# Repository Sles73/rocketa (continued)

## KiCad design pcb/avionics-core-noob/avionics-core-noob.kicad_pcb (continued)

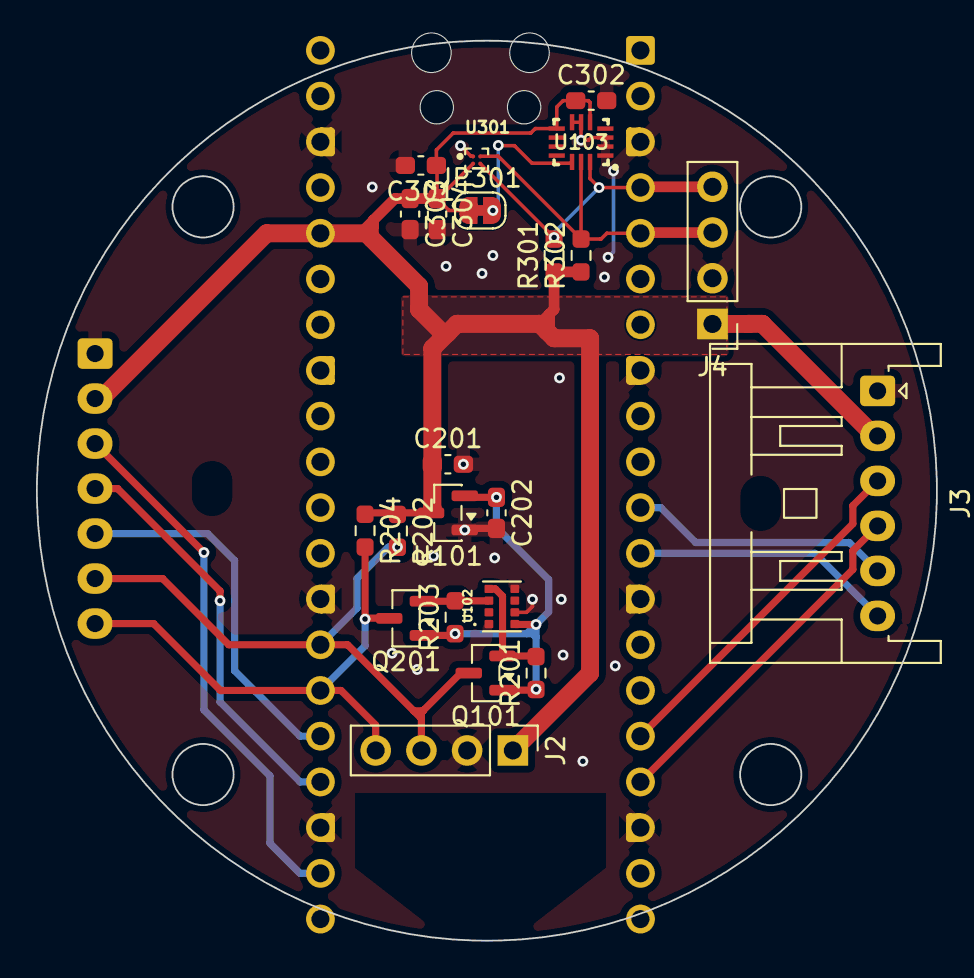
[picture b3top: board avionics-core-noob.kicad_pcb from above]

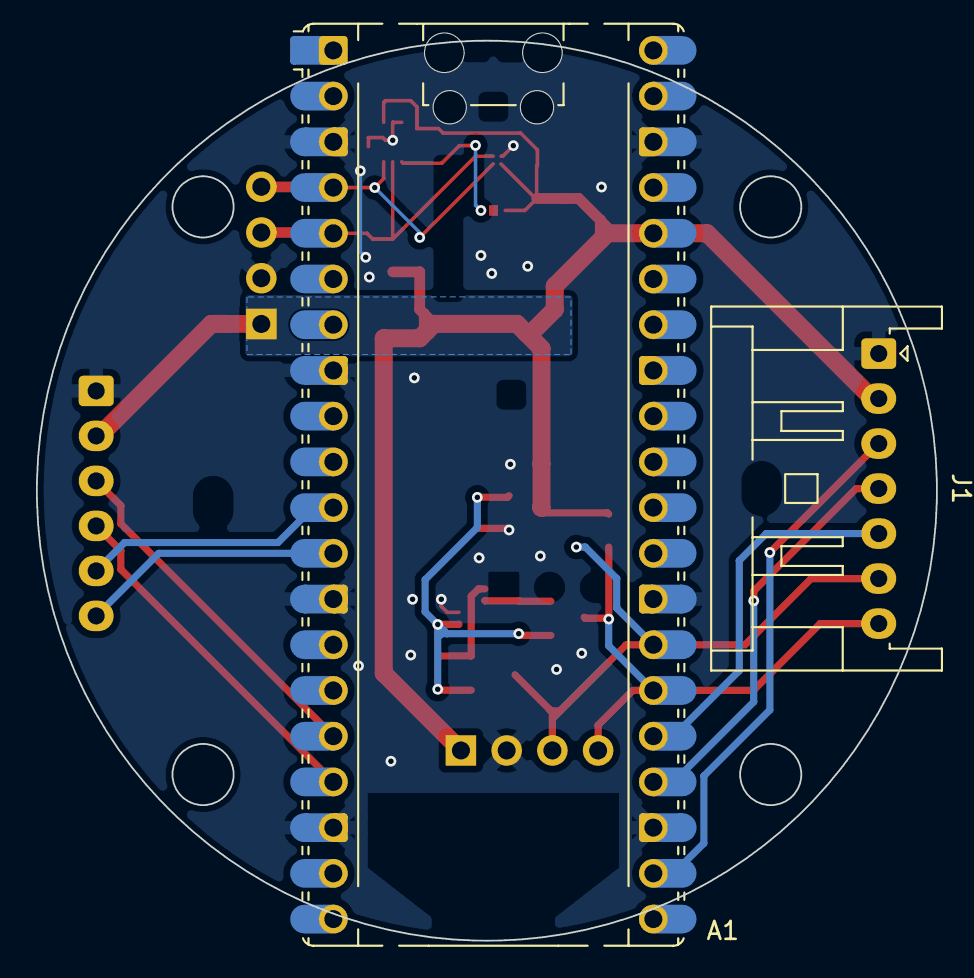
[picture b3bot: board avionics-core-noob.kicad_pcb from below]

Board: 2 copper layers, 50.0 x 50.0 mm, 24 parts (2 on the bottom side), 17 nets.

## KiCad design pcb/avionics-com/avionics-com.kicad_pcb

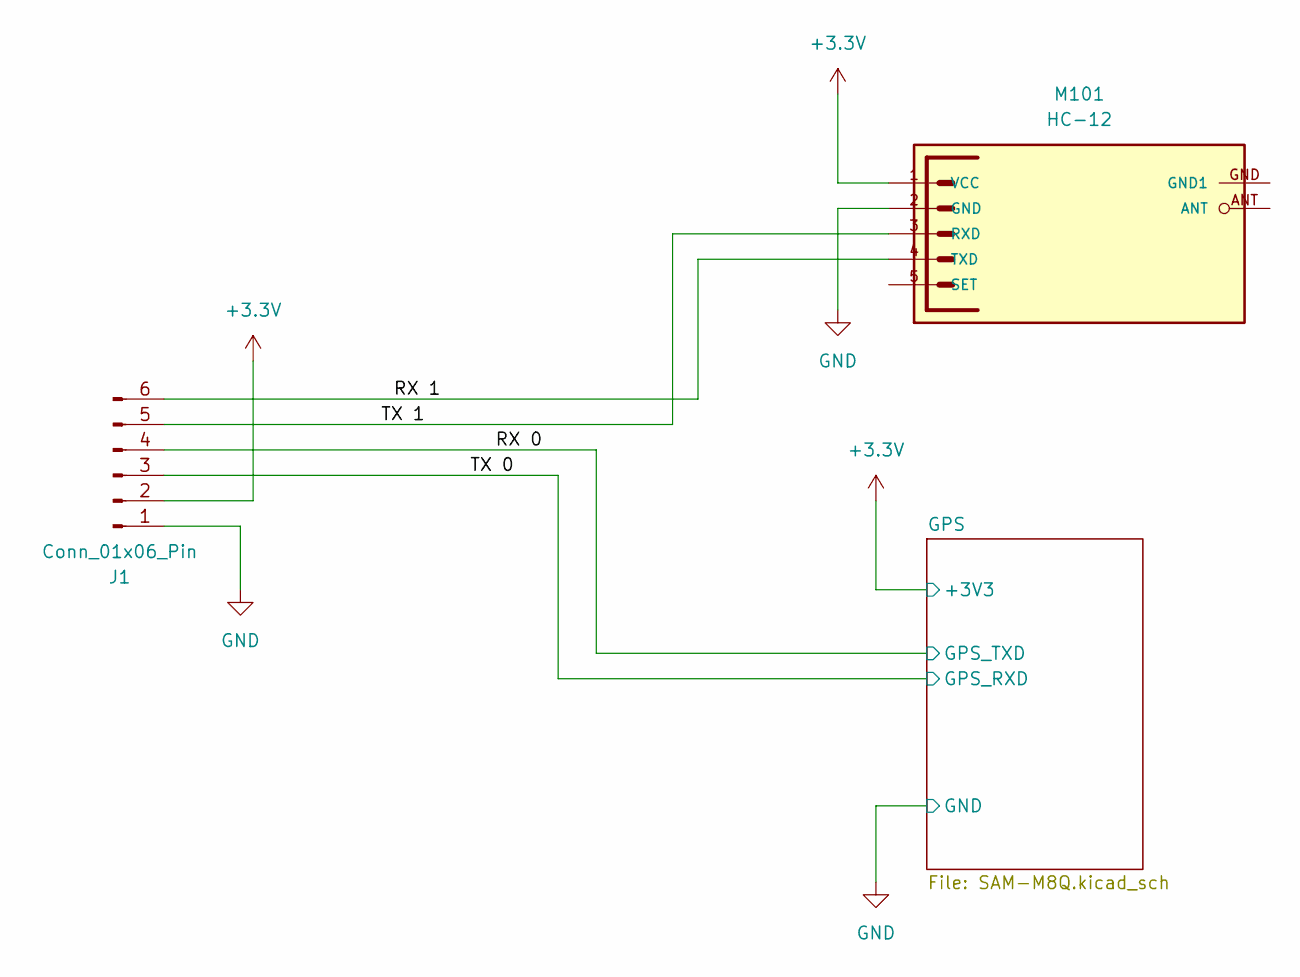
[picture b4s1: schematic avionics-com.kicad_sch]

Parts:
J1: Conn_01x06_Pin; JST_XA_S06B-XASK-1_1x06_P2.50mm_Horizontal
M101: HC-12; MA05-1

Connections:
+3.3V: J1.2, M101.1 (VCC); also elsewhere on the board
/RX 0: J1.4; also elsewhere on the board
/RX 1: J1.6, M101.4 (TXD)
/TX 0: J1.3; also elsewhere on the board
/TX 1: J1.5, M101.3 (RXD)
GND: J1.1, M101.2 (GND); also elsewhere on the board
unnamed: M101.GND (GND1), M101.GND1

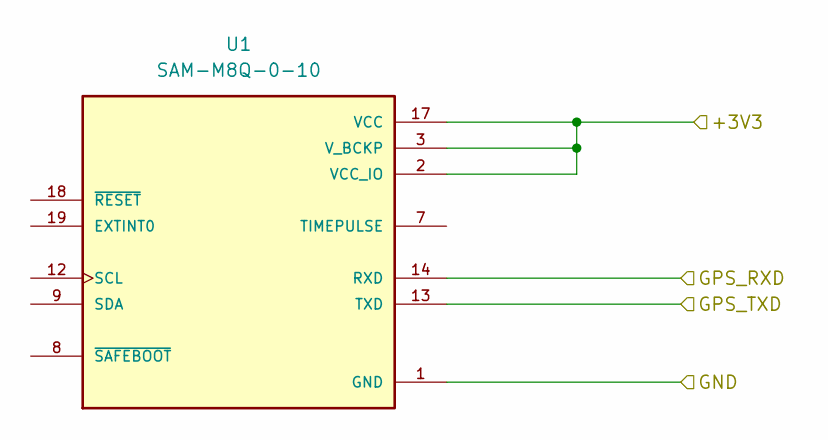
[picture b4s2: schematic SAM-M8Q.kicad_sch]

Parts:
U1: SAM-M8Q-0-10; MODULE_SAM-M8Q-0-10; PARTREV R07

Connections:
+3.3V: U1.2 (VCC_IO), U1.3 (V_BCKP), U1.17 (VCC); also elsewhere on the board
/RX 0: U1.13 (TXD); also elsewhere on the board
/TX 0: U1.14 (RXD); also elsewhere on the board
GND: U1.1 (GND), U1.4 (GND), U1.5 (GND), U1.6 (GND), U1.10 (GND), U1.11 (GND), U1.15 (GND), U1.16 (GND), U1.20 (GND); also elsewhere on the board

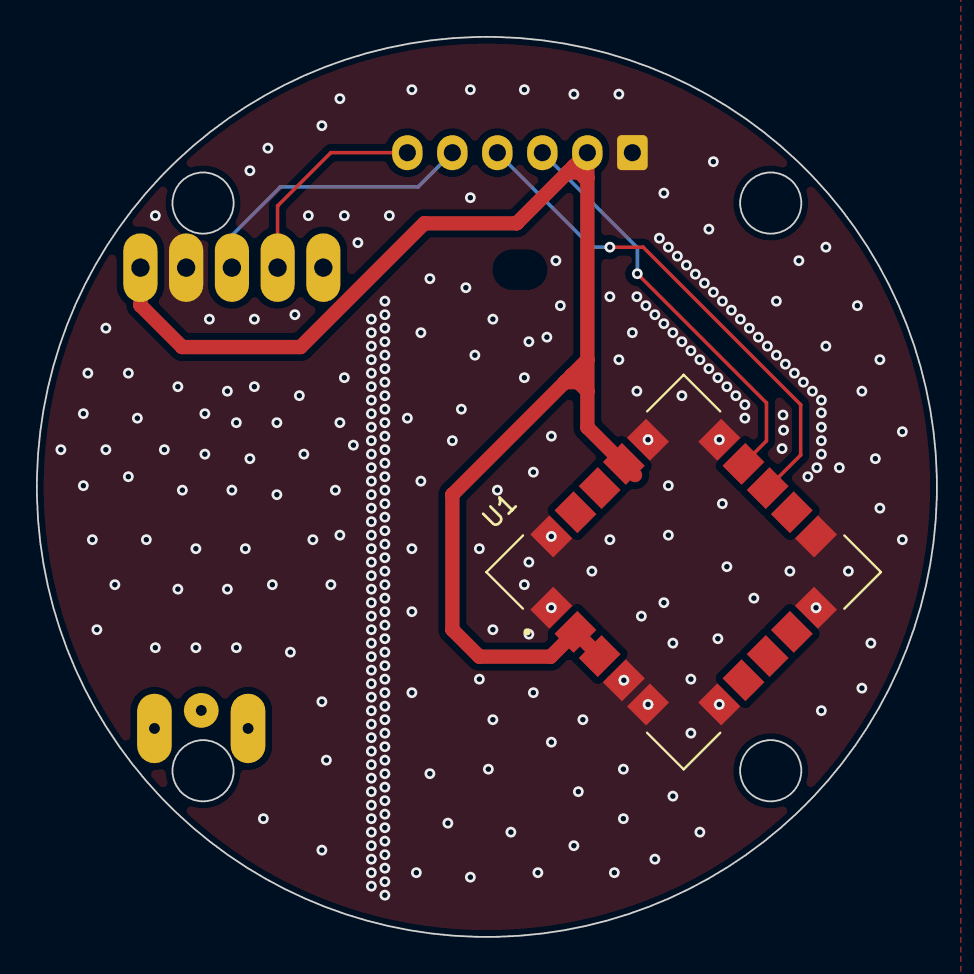
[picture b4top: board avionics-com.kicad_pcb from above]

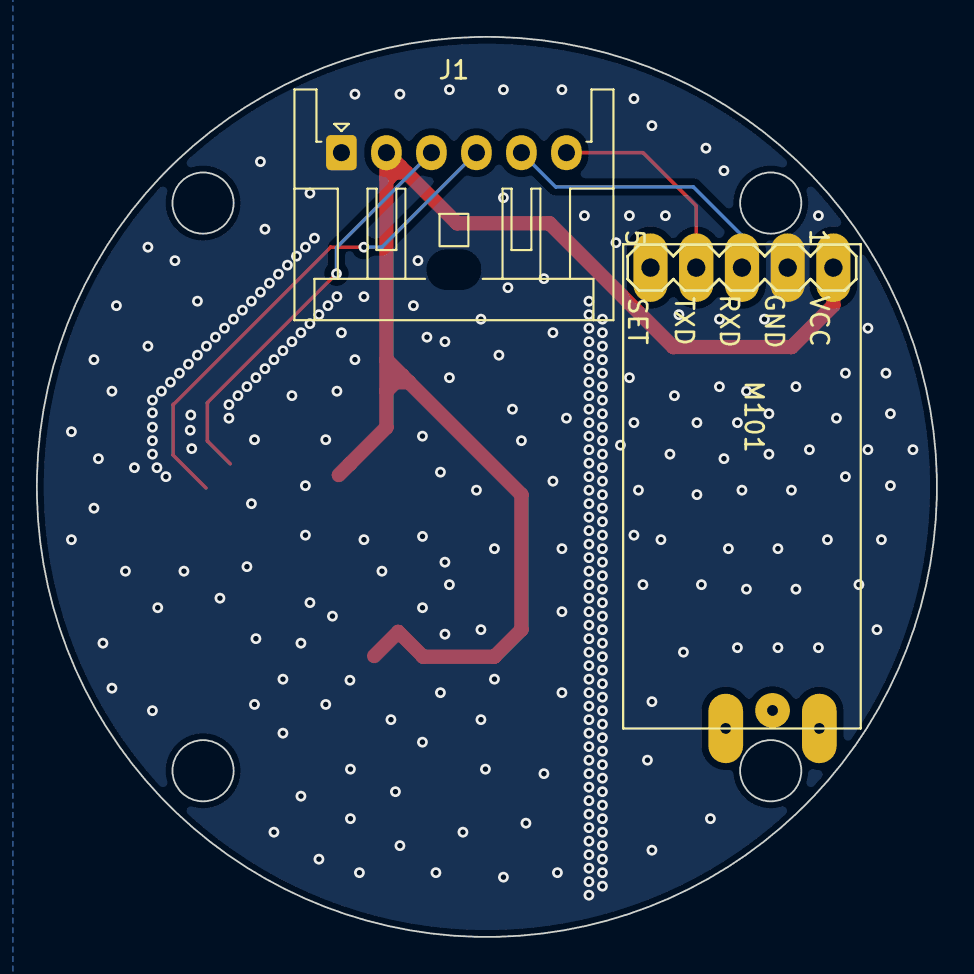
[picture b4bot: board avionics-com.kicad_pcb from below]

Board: 2 copper layers, 50.0 x 50.0 mm, 3 parts (2 on the bottom side), 7 nets.

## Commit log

2026-05-04 open rocket file innit
2026-05-12 draft finaloveho reportu
2026-05-12 core boom
